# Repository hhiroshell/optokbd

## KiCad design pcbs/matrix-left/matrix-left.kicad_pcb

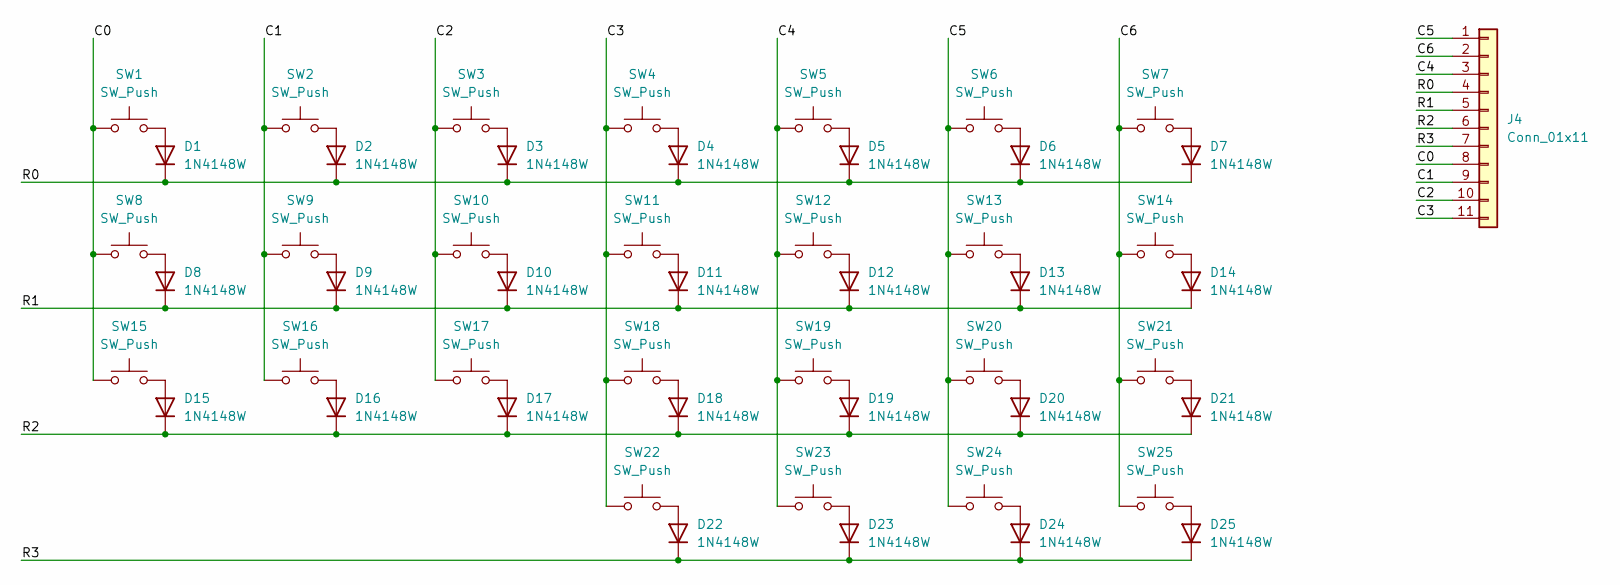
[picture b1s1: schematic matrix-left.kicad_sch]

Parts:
D1, D2, D3, D4, D5, D6, D7, D8, D9, D10, D11, D12, D13, D14, D15, D16, D17, D18, D19, D20, D21, D22, D23, D24, D25: 1N4148W; D_SOD-123; LCSC C81598
J4: Conn_01x11; JST_SH_SM11B-SRSS-TB_1x11-1MP_P1.00mm_Horizontal; LCSC C515956
SW1, SW2, SW3, SW4, SW5, SW6, SW7, SW8, SW9, SW10, SW11, SW12, SW13, SW14, SW15, SW16, SW17, SW18, SW19, SW20, SW21, SW22, SW23, SW24, SW25: SW_Push; CherryMX_Hotswap_1u; LCSC C41430893

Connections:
/C0: J4.8, SW1.1, SW8.1, SW15.1
/C1: J4.9, SW2.1, SW9.1, SW16.1
/C2: J4.10, SW3.1, SW10.1, SW17.1
/C3: J4.11, SW4.1, SW11.1, SW18.1, SW22.1
/C4: J4.3, SW5.1, SW12.1, SW19.1, SW23.1
/C5: J4.1, SW6.1, SW13.1, SW20.1, SW24.1
/C6: J4.2, SW7.1, SW14.1, SW21.1, SW25.1
/R0: D1.1 (K), D2.1 (K), D3.1 (K), D4.1 (K), D5.1 (K), D6.1 (K), D7.1 (K), J4.4
/R1: D8.1 (K), D9.1 (K), D10.1 (K), D11.1 (K), D12.1 (K), D13.1 (K), D14.1 (K), J4.5
/R2: D15.1 (K), D16.1 (K), D17.1 (K), D18.1 (K), D19.1 (K), D20.1 (K), D21.1 (K), J4.6
/R3: D22.1 (K), D23.1 (K), D24.1 (K), D25.1 (K), J4.7
unnamed: D1.2 (A), SW1.2
unnamed: D2.2 (A), SW2.2
unnamed: D3.2 (A), SW3.2
unnamed: D4.2 (A), SW4.2
unnamed: D5.2 (A), SW5.2
unnamed: D6.2 (A), SW6.2
unnamed: D7.2 (A), SW7.2
unnamed: D8.2 (A), SW8.2
unnamed: D9.2 (A), SW9.2
unnamed: D10.2 (A), SW10.2
unnamed: D11.2 (A), SW11.2
unnamed: D12.2 (A), SW12.2
unnamed: D13.2 (A), SW13.2
unnamed: D14.2 (A), SW14.2
unnamed: D15.2 (A), SW15.2
unnamed: D16.2 (A), SW16.2
unnamed: D17.2 (A), SW17.2
unnamed: D18.2 (A), SW18.2
unnamed: D19.2 (A), SW19.2
unnamed: D20.2 (A), SW20.2
unnamed: D21.2 (A), SW21.2
unnamed: D22.2 (A), SW22.2
unnamed: D23.2 (A), SW23.2
unnamed: D24.2 (A), SW24.2
unnamed: D25.2 (A), SW25.2

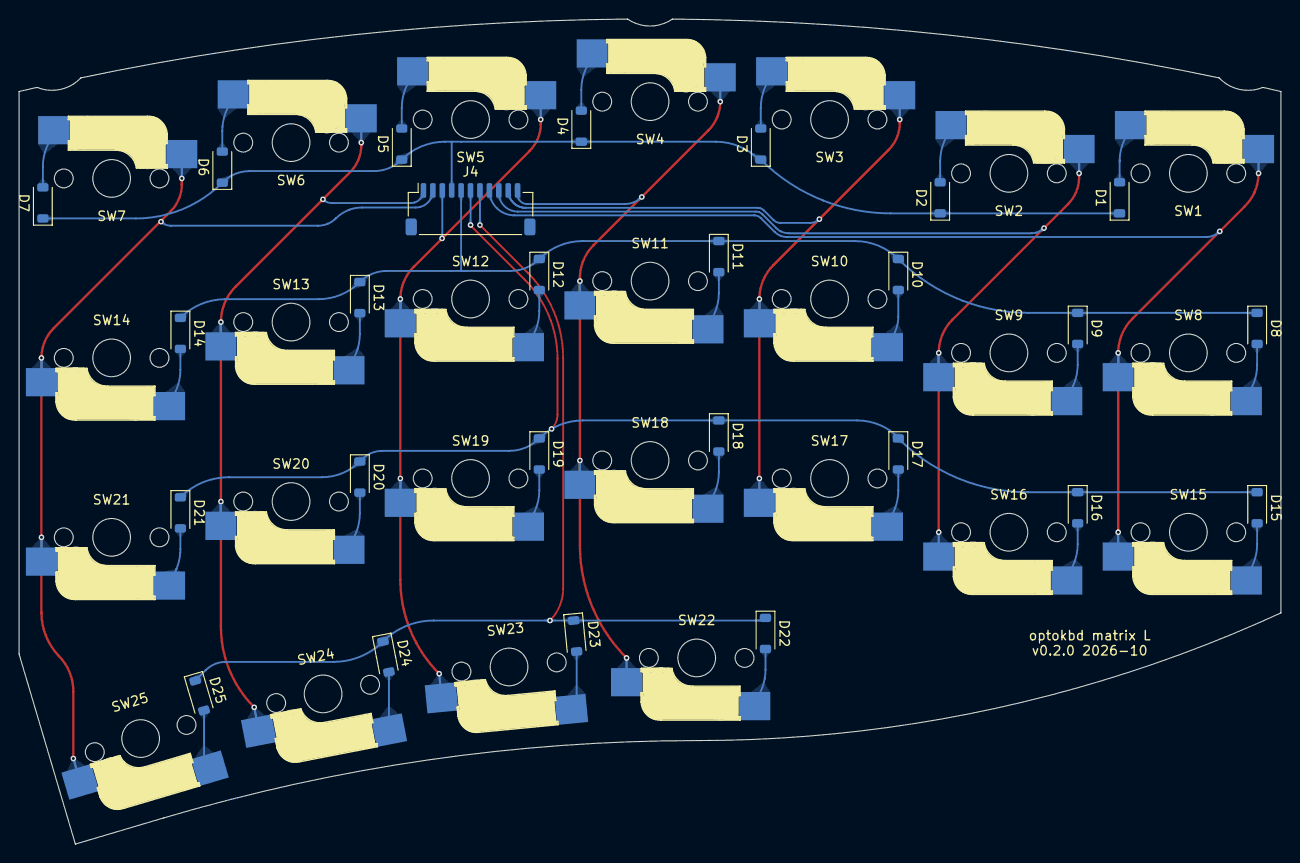
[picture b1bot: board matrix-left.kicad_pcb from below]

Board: 2 copper layers, 134.0 x 87.6 mm, 51 parts (26 on the bottom side), 36 nets.

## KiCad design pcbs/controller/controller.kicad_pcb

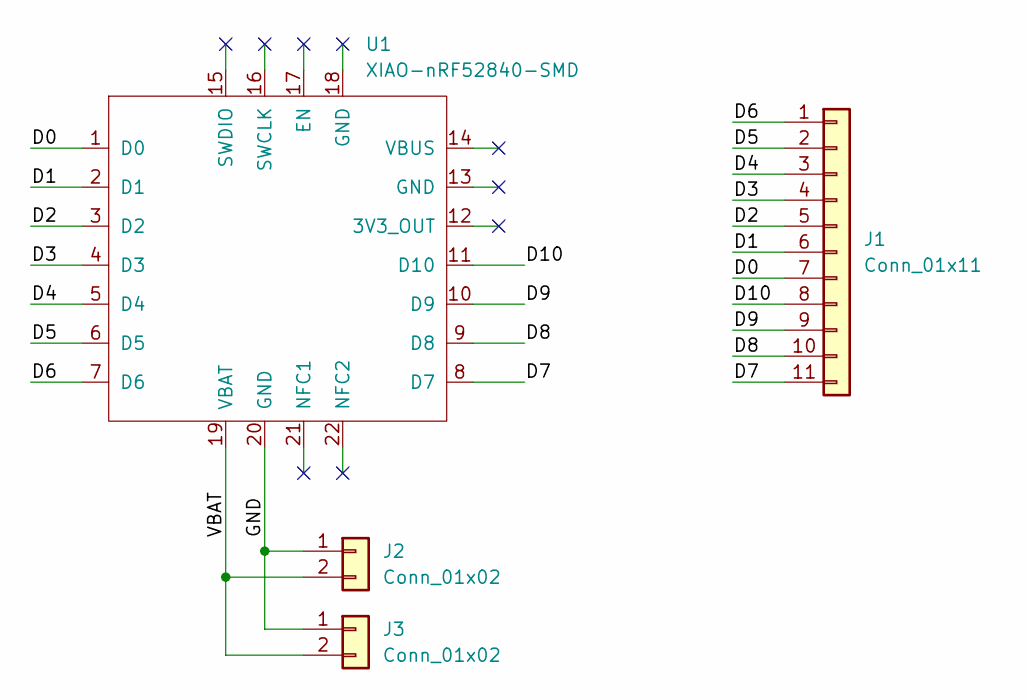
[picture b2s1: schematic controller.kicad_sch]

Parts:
J1: Conn_01x11; JST_SH_SM11B-SRSS-TB_1x11-1MP_P1.00mm_Horizontal
J2, J3: Conn_01x02; JST_PH_S2B-PH-K_1x02_P2.00mm_Horizontal
U1: XIAO-nRF52840-SMD; modified-XIAO-nRF52840-SMD

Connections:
/D0: J1.7, U1.1 (D0)
/D1: J1.6, U1.2 (D1)
/D2: J1.5, U1.3 (D2)
/D3: J1.4, U1.4 (D3)
/D4: J1.3, U1.5 (D4)
/D5: J1.2, U1.6 (D5)
/D6: J1.1, U1.7 (D6)
/D7: J1.11, U1.8 (D7)
/D8: J1.10, U1.9 (D8)
/D9: J1.9, U1.10 (D9)
/D10: J1.8, U1.11 (D10)
/GND: J2.1, J3.1, U1.20 (GND)
/VBAT: J2.2, J3.2, U1.19 (VBAT)

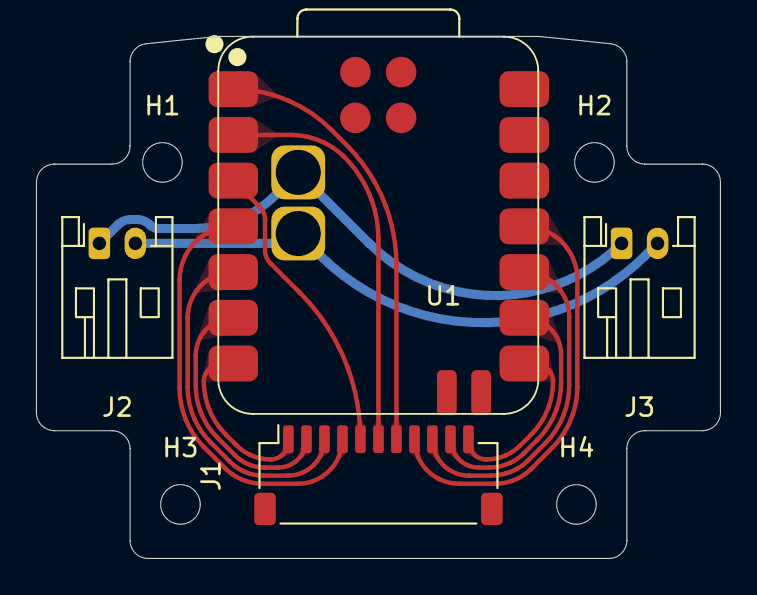
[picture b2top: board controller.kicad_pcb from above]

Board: 2 copper layers, 38.0 x 29.0 mm, 8 parts (0 on the bottom side), 13 nets.

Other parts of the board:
H1, H2, H3, H4: MountingHole_2.2mm_M2

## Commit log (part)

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2026-05-25 Add keyboard case design files
